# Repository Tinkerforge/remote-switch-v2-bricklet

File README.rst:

Remote Switch Bricklet 2.0
==========================

This repository contains the firmware source code and the hardware design
files. The documentation generator configs can be found at
https://github.com/Tinkerforge/generators

Repository Content
------------------

software/:
 * examples/: Examples for all supported languages
 * build/: Compiled files
 * src/: Source code of firmware
 * Makefile: Makefile to build project

hardware/:
 * Contains KiCad project files and additionally schematics as PDF

datasheets/:
 * Contains datasheets for sensors and complex ICs that are used

Hardware
--------

The hardware is designed with the open source EDA Suite KiCad
(http://www.kicad.org). Before you are able to open the files,
you have to install the Tinkerforge kicad-libraries
(https://github.com/Tinkerforge/kicad-libraries). You can either clone
them directly in hardware/ or clone them in a separate folder and
symlink them into hardware/
(ln -s kicad_path/kicad-libraries project_path/hardware). After that you
can open the .pro file in hardware/ with KiCad and from there view and
modify the schematics and the PCB layout.

Software
--------

If you want to do your own Brick/Bricklet firmware development we highly
recommend that you use our build environment setup script and read the
tutorial (https://www.tinkerforge.com/en/doc/Tutorials/Tutorial_Build_Environment/Tutorial.html).

To compile the C code we recommend you to install the newest GNU Arm Embedded
Toolchain (https://launchpad.net/gcc-arm-embedded/+download).
You also need to install bricklib2 (https://github.com/Tinkerforge/bricklib2).

You can either clone it directly in software/src/ or clone it in a
separate folder and symlink it into software/src/
(ln -s bricklib_path/bricklib2 project_path/software/src/). Finally make sure to
have CMake installed (http://www.cmake.org/cmake/resources/software.html).

After that you can build the firmware by invoking make in software/.
The firmware (.zbin) can then be found in software/build/ and uploaded
with brickv (click button "Flashing" on start screen).

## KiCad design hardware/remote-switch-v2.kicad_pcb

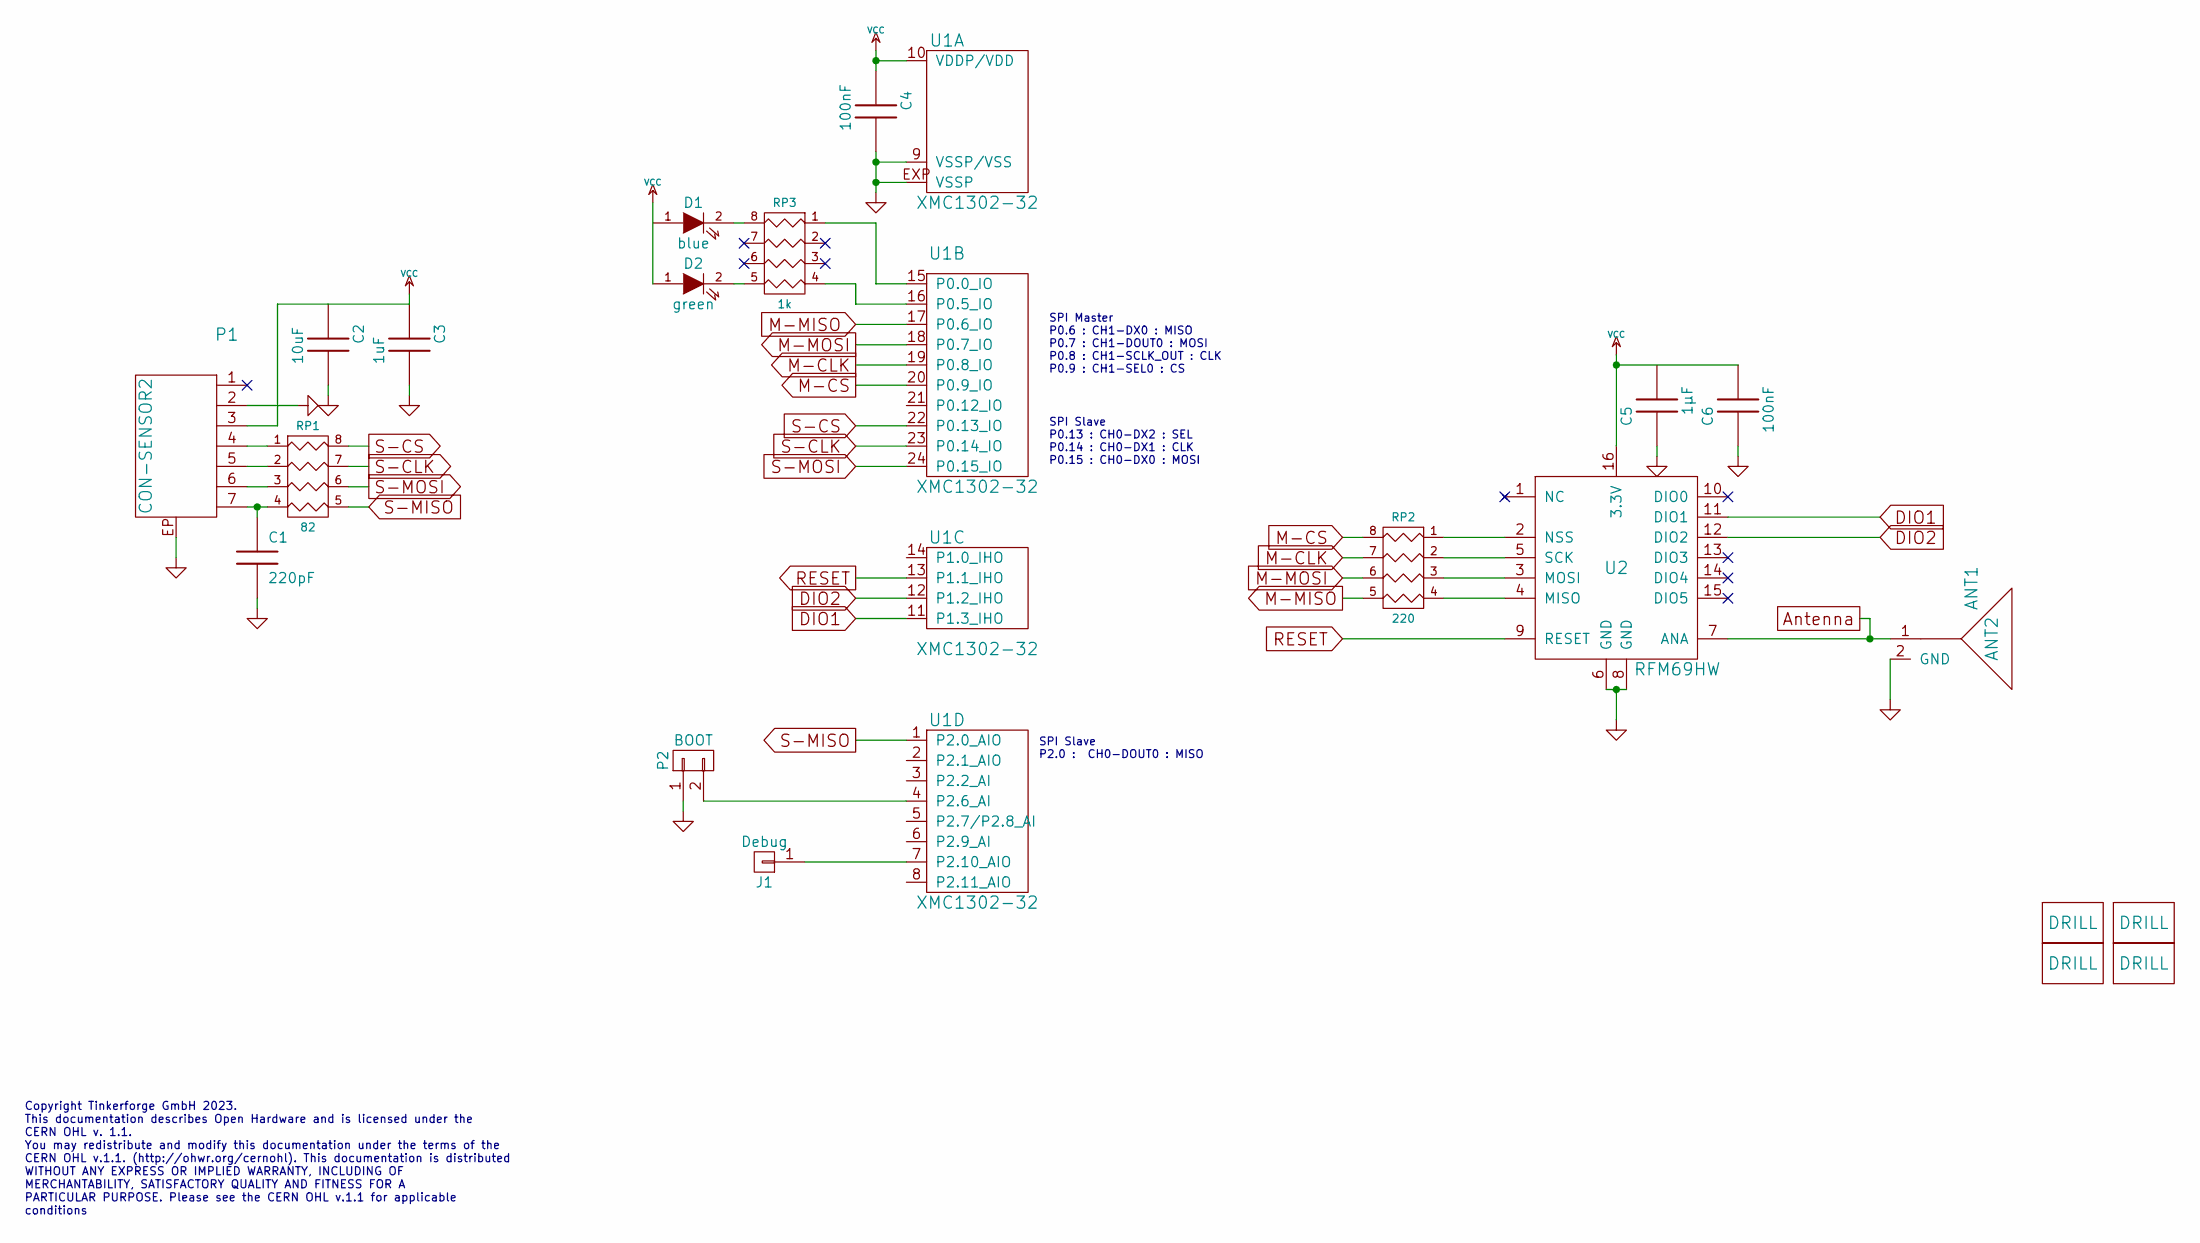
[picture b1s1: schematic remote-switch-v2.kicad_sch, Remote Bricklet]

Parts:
ANT1: ANT2; FT-004B
C1: 220pF; C0402F
C2: 10uF; C0805
C3: 1uF; C0603F
C4, C6: 100nF; C0603F
C5: 1µF; C0603F
D1: blue; D0603F
D2: green; D0603F
J1: Debug; DEBUG_PAD
P1: CON-SENSOR2
P2: BOOT; SolderJumper
RP1: 82; 4X0402
RP2: 220; 4X0603
RP3: 1k; 4X0603
U1: XMC1302-32; QFN24-4x4mm-0.5mm
U2: RFM69HW
U3, U4, U5, U6: DRILL; DRILL_NP

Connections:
Antenna: ANT1.1, U2.7 (ANA)
DIO1: U1.11 (P1.3_IHO), U2.11 (DIO1)
DIO2: U1.12 (P1.2_IHO), U2.12 (DIO2)
GND: ANT1.2 (GND), C1.2, C2.2, C3.2, C4.2, C5.1, C6.1, P1.2, P1.EP, P2.1, U1.9 (VSSP/VSS), U1.EXP (VSSP), U2.6 (GND), U2.8 (GND)
M-CLK: RP2.7 (R2), U1.19 (P0.8_IO)
M-CS: RP2.8 (R1), U1.20 (P0.9_IO)
M-MISO: RP2.5 (R4), U1.17 (P0.6_IO)
M-MOSI: RP2.6 (R3), U1.18 (P0.7_IO)
unnamed: C1.1, P1.7, RP1.4
unnamed: D1.2 (K), RP3.8 (R1)
unnamed: D2.2 (K), RP3.5 (R4)
unnamed: J1.1, U1.7 (P2.10_AIO)
unnamed: P1.4, RP1.1
unnamed: P1.5, RP1.2
unnamed: P1.6, RP1.3
unnamed: P2.2, U1.4 (P2.6_AI)
unnamed: RP2.1, U2.2 (NSS)
unnamed: RP2.2, U2.5 (SCK)
unnamed: RP2.3, U2.3 (MOSI)
unnamed: RP2.4, U2.4 (MISO)
unnamed: RP3.1, U1.15 (P0.0_IO)
unnamed: RP3.4, U1.16 (P0.5_IO)
RESET: U1.13 (P1.1_IHO), U2.9 (RESET)
S-CLK: RP1.7 (R2), U1.23 (P0.14_IO)
S-CS: RP1.8 (R1), U1.22 (P0.13_IO)
S-MISO: RP1.5 (R4), U1.1 (P2.0_AIO)
S-MOSI: RP1.6 (R3), U1.24 (P0.15_IO)
VCC: C2.1, C3.1, C4.1, C5.2, C6.2, D1.1 (A), D2.1 (A), P1.3, U1.10 (VDDP/VDD), U2.16 (3.3V)

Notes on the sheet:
SPI Slave P0.13 : CH0-DX2 : SEL P0.14 : CH0-DX1 : CLK P0.15 : CH0-DX0 : MOSI
Copyright Tinkerforge GmbH 2023. This documentation describes Open Hardware and is licensed under the CERN OHL v. 1.1. You may redistribute and modify this documentation under the terms of the CERN OHL v.1.1. (http://ohwr.org/cernohl). This documentation is distributed WITHOUT ANY EXPRESS OR IMPLIE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
SPI Master P0.6 : CH1-DX0 : MISO P0.7 : CH1-DOUT0 : MOSI P0.8 : CH1-SCLK_OUT : CLK P0.9 : CH1-SEL0 : CS
SPI Slave P2.0 : CH0-DOUT0 : MISO

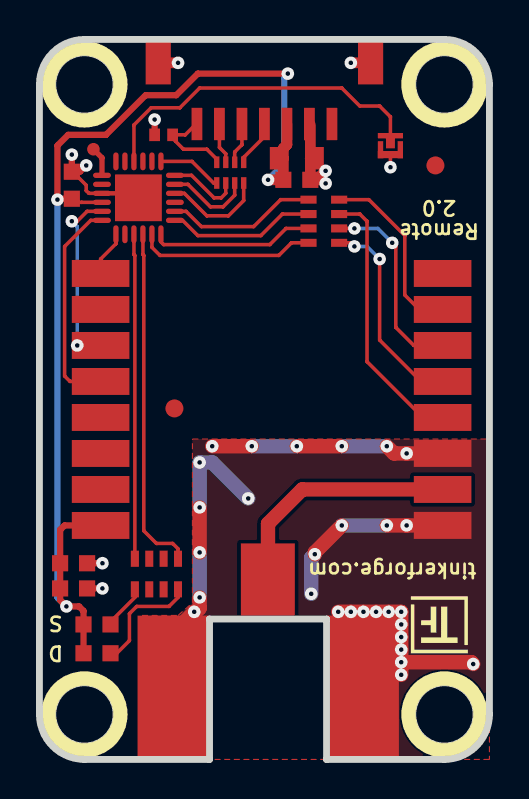
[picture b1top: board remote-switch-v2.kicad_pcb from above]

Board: 2 copper layers, 25.0 x 40.0 mm, 25 parts (2 on the bottom side), 28 nets.

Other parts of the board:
Fiducial_Mark: VAL**; Fiducial_Mark
Fiducial_Mark#2: VAL**; Fiducial_Mark
VAL: CE_5mm
VAL#2: WEEE_7mm

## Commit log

2017-09-05 Add initial stub version
2017-09-05 Add readme
2017-09-08 Add implementation of old API
2017-09-13 major parts of remote switch bricklet v2 schematic finished
2017-09-13 add dio signals
2017-09-14 finished prototype
2017-09-15 Add support for receive of remotes
2017-09-18 fix capacitor footprints
2017-09-18 Add support for remote type B and C
2017-09-18 Remove debug
2017-09-28 fix bootpad name
2017-09-28 specify processor
2017-09-28 add debug pad
2017-09-29 Change MCU to XMC1300
2017-09-29 Use led for debug
2017-09-29 Set pins as used in production board
2017-10-26 move text to fab layer
2017-11-24 specify led colors
2018-01-11 Do not allow min repeats of zero
2018-01-11 Add examples
2018-01-11 Change data type of minimum_repeats (uint8 -> uint16)
2018-01-11 Fix input check
2018-01-15 examples: Add missing remote config call
2018-01-16 Fix pointer access
2018-01-16 Return empty configuration if the remote type is not currently configured
2018-01-16 Use correct slave select (0 instead of 4)
2018-01-16 Add logging on startup
2018-01-16 Remove unused variable
2018-01-25 fix broken mounting holes
2018-01-26 c: Fine-tune printf format
2018-02-01 Fix egde cuts
2018-02-01 Add 3d information (final)
2018-02-01 Add 3d model (*.step & *.FCStd)
2018-02-16 Fix symbol (CONN_01X01)
2018-02-16 Add schematic PDF
2018-02-19 javascript: Close div tag correctly
2018-02-20 Cleanup KiCad libraries config
    Ensure LibDir=kicad-libraries and LibName1=tinkerforge.
    Remove special library.
2018-02-28 Add new 3d model with more detailed components
2018-03-02 Fix outline from antenna connector larger caused thru production tolerance
2018-03-09 fix miso configuration
2018-03-15 Use P2_10 for debugging (was changed in production unit)
2018-03-15 Remove unused ";"
2018-03-15 RFM69 expects passive level 0 spi
2018-03-15 Interpret 2x oversampled input as "analog values" and allow some inaccuracies in the protocol. In tests we found that the bit rate from remote to remote can differ by ~25%. Example: If we expect a "1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
    This approach works _much_ better in our tests!
2018-03-15 Increase firmware version, add changelog entry (2.0.1)
2018-05-11 Rename files
2018-05-24 perl: Use strict in examples
2018-05-28 mathematica: Fix namespace
2018-06-07 Add LabVIEW examples
2018-06-18 Change capacitor footprint(s) to C0402F
2018-06-28 Fix readme
2018-07-11 Add Makefile with docker support
2018-07-11 Remove obsolete generate_makefile scripts
2018-07-11 Update directory structure and build instructions
2018-10-04 Increase version for new release (changes in bricklib2)
2018-10-04 Add rev to changelog
2018-11-06 Add rust examples
2018-11-07 rust: Accept host names for ip connection, fix naming inconsistencies
2018-11-07 rust: Rename callback receivers.
2018-12-14 Add go examples.
2018-12-18 go: Change import path.
2018-12-18 go: Change import path again.
2018-12-20 Fix constant handling in examples.
2018-12-20 rust: Reformat examples.
2019-01-24 mqtt: Add examples.
2019-01-24 mqtt: Fix example header.
2019-01-24 mqtt: Remove executable bit in example permissions.
2019-01-24 go: Minor example fixes.
2019-01-24 mqtt: Minor example fixes.
2019-08-22 c: Adapt to bindings changes
2020-01-13 examples: Use python3 input instead of python2 raw_input.
2020-01-13 examples: mqtt: Remove trailing whitespace.
2020-03-16 Whitespace
2020-04-07 examples: rust: Always block when calling bindings functions.
2020-08-19 Add uc examples.
2020-08-25 uc: Fix whitespace
2020-08-27 uc: Fix warnings.
2020-08-31 uc: Use fixed-with placeholders in format strings.
2020-09-02 uc: Add example driver note.
2021-10-25 Update KiCad link
    https://www.kicad.org/blog/2021/10/Avoid-links-to-former-kicad-domain/
2022-04-19 examples: uc: Rename TF_HalContext to TF_HAL.
2022-04-27 uc: Adapt to bindings changes
2022-07-06 Add license files.
2023-01-27 fix schamtic
2023-01-27 Data Cleanup
2025-10-04 Fix compatibility with new Docker build image (GCC 14.2.1)

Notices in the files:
hardware/remote-switch-v2.kicad_pcb:
Licensed under CERN OHL v.1.1
Copyright (©) 2023, B.Nordmeyer
